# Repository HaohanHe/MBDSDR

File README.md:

# MBDSDR · AI 定义无线电（AI-defined SDR） v0.2.0

> **30 秒读懂**：这是一套把示波器/矢网/软件无线电（SDR）的每个动作封装成
> LLM 可调用工具的系统——外部 AI agent 通过 MCP 协议直接遥控真实硬件：
> 测天线、收信号、解调、解码、抓星历。**没有 mock、没有假数据**：没插硬件
> 就报空，未校准就标口径。本页「快速开始」的离线命令在隔离环境实测过，
> 实测口径与自动化契约见 [§4 离线复验](#4-离线复验本页命令的实测口径) 与 [`scripts/verify_readme.py`](scripts/verify_readme.py)。
>
> **真机实证（2026-10）**：NanoVNA-H 实测自制天线谐振与馈线时延、
> RTL-SDR 实抄 435MHz 业余频段载波、外部 agent 经 MCP 遥控收发全链路、
> 设备屏幕截图回传——全部见 [`docs/learn/agent-onboarding-runbook.md`](docs/learn/agent-onboarding-runbook.md)。

把 SDR 的接收 / 解调 / 解码 / 卫星过境 / AR 指向，全部封装成 LLM 可调用的工具（function calling），
由智能体编排成"一键工作流"。本仓库是同一套体系在**桌面（两套实现）、手机端、Python 智能体内核，
外加论文实验管线与真机工具**上的落地；不写死组件数量，实时清单以本节表格为准。

| 组件 | 位置 | 是什么 |
|---|---|---|
| Python/PySide6 桌面客户端 | [`desktop/`](desktop/README.md) | 持续维护中的完整桌面端：频谱/瀑布、星象仪全天球、AI 对话栏、真机接收链。`python desktop/main.py` 直接启动、无需编译；无硬件时默认显示诚实「未连接」空状态 |
| 原生 C++/Qt 桌面端 | [`cpp/`](cpp/README.md) | C++/Qt 原生 SDR 接收软件（UI 与 DSP 同进程，不依赖 Python 运行时）。AI 助手工具面（read/write 双态、写动作在手动模式被门拦截；**数量随版本漂移，实时口径以 `cpp/src/ai/tool_schema.cpp` 注册表为准**），并内置 ControlHub HTTP 控制通道 |
| 手机端 | [`mobile/`](mobile/README.md) | Flutter 一套代码（Android/iOS），手机作 AI 的"眼睛和手臂"：定位+罗盘指向+rtl_tcp 直连外置 SDR；经 ControlHub HTTP 只读对接桌面引擎 |
| Python 智能体内核 | [`mbdsdr_ai/`](mbdsdr_ai/README.md) | **研究原型**：注册大量 LLM 可调用工具（数量随版本漂移，实时口径见该 README §1 与运行时 `tool_registry.list_tools()`）+ 工作流引擎。这是原型期工具面，**不是**随桌面交付的工具集 |
| 论文实验管线 | [`experiments/`](experiments/README.md) | 可复现实验（Eb/N0 解码成功率 / 多普勒定轨 / AMR 基线 / LLM 基线），固定种子、逐图标口径 |
| 真机工具 | [`tools/`](tools/) | 一键只读自检 `hw_selfcheck` + 联调向导 `onboarding` |
| 重复实现台账 | [`docs/learn/dedup-ledger.md`](docs/learn/dedup-ledger.md) | 同主题多份实现的状态台账（已收敛/有意分层/待收敛）+ 成对工具自洽审计方法与已修缺陷 | 
| 能力地图 | [`docs/learn/capability-map.md`](docs/learn/capability-map.md) | 任务→积木编排对照表（气象对星接收/多普勒定轨/ASTU-1遥测/前端搭建/链路自测）+ 新积木参数速查 + 诚实边界 |
| 学习与阶段规格 | [`docs/learn/`](docs/learn/) | 上游真实源码精读（sdrpp/gnuradio/librtlsdr…）+ phase3–6 实现规格与审计 |

许可证：**MIT**（见 [`LICENSE`](LICENSE)、第三方归属 [`NOTICE.md`](NOTICE.md)）。

**工程口径**：全仓 **MIT 发布**，第三方上游项目与许可归属见 [`NOTICE.md`](NOTICE.md)；
协议栈（FT8/LRPT/CCSDS 等）按公开标准与协议事实独立实现 · LLM 工具三通道（Agent / ControlHub /
HTTP）行为一致且有测试钉住，写动作一律过人工门 · 已对 SDR++、SatDump、
nanovna-saver、NanoVNA-App、kimi-code、kilocode 六个上游项目做过源码级
克隆审计（见 [`docs/learn/`](docs/learn/)）。

---

<details open>
<summary><b>日本語 / For Japanese readers</b></summary>

**MBDSDR は「AI が計測器を直接操作するシステム」です。** SDR（ソフトウェア無線）と
ベクトル・ネットワーク・アナライザ（NanoVNA）の操作を LLM から呼び出せる
ツールとして実装し、MCP（Model Context Protocol）経由で外部エージェントが
実機を操作できます。専用機器の操作習熟コストを AI に引き渡すことが出発点です。

**実機検証済み（2026 年 10 月、ダミーデータなし）**：
NanoVNA-H による自作アンテナの共振周波数・給線路遅延の実測 / RTL-SDR による
435 MHz 帯アマチュア周波数の実キャリア受信・FM 復調 / 外部エージェントからの
MCP 遠隔操作（list_devices → connect → set_frequency → get_status）。

**ライセンスと門**：リポジトリ全体が MIT（独立実装、GPL コードの流用なし）·
LLM ツールは Agent / ControlHub / HTTP の 3 チャネルで動作が一致し、書き込みには
手動承認ゲートが必須 · SDR++・SatDump・NanoVNA-App 等の主要 OSS をクローンして
ソース監査済み。

ハードウェアなしで試す：
`python3 -m mbdsdr_ai.aigui_demo --out demo.html`（AI 編排 UI の一巡）、
`python3 -m pytest tools/hw_selfcheck/test_selfcheck.py tools/onboarding/test_onboarding.py -q`
（オフライン決定性テスト）。どちらも実機を必要としません。

</details>

---

## 快速开始

### 1. 桌面端（两套实现，按工具链选）

**Python / PySide6 桌面客户端**——无需 C++ 工具链，当前持续维护的 UI 主界面：

```bash
pip install -r requirements.txt
python desktop/main.py                                     # 无硬件时显示诚实「未连接」空状态
python desktop/main.py --theme dark                        # 可选：default / dark / high_contrast
python desktop/main.py --import-probe desktop.main_window  # 只做导入自检，不建窗口
```

依赖、打包与其它启动方式见 [`desktop/README.md`](desktop/README.md)。
不插硬件时**不默认造合成 IQ**；`--import-probe` 是在无显示环境里验证安装的最快一条命令。

**原生 C++/Qt 桌面端**——需 Qt 6.8 / librtlsdr 2.x / CMake 3.16+ 与 C++ 编译工具链：

```bash
cd cpp
cmake -S . -B build && cmake --build build -j"$(nproc)"
./build/mbdsdr        # 无硬件且未加载离线捕获文件时，显示诚实"未连接"空状态
                      # 需要合成调试信号时必须显式 --test-source / MBDSDR_TEST_SOURCE=1
                      # 设计红线：never invent synthetic IQ by default, no fake hardware is ever shown
```

依赖、测试与完整功能清单见 [`cpp/README.md`](cpp/README.md)。
两套桌面端并存、各有独立测试；没有 C++ 工具链的机器直接走上面的 Python 端，不必先编 `cpp/`。

**原生 C++/Qt 桌面端**启动后在**回环 `127.0.0.1:50732`** 起一条 ControlHub HTTP 控制通道
（具名常量 `cpp/src/core/tokens.h` 的 `kControlHttpDefaultPort`，QSettings/env 可配）：
本机浏览器开 `http://127.0.0.1:50732/` 即可查看状态 / 下命令；端点只绑回环，跨机控制走 SSH 隧道（如 `ssh -N -L 50732:127.0.0.1:50732 user@接收机`）。
Chromebook / Crostini 当远程控制端的完整拓扑与隧道步骤见 [`docs/CHROMEOS_CROSTINI_SDR.md`](docs/CHROMEOS_CROSTINI_SDR.md)。
Python/PySide6 桌面端不走这条 ControlHub 通道，别按上面的地址去找它。

### 2. 真机自检 + 联调（一条命令）

真机（RTL-SDR + GNSS + 天线）在**用户本地**；云开发环境无任何硬件透传：

```bash
# 只读自检：USB/udev、rtl_test tuner、rtl_sdr 实读丢包、声卡、GNSS 串口、Python 依赖
python3 tools/hw_selfcheck/selfcheck.py

# 一条命令从"插好 RTL-SDR"走到"出图/出报文"（ADS-B 飞机报文，1090 MHz）
python3 tools/onboarding/onboard.py --step all --freq 1090e6 --mode adsb
```

- 两条命令都可加 `--json` 输出结构化结果；**无硬件时每步明确失败原因，绝不 mock、绝不造假数据**。
- 真机用户跑完后，按 [`docs/learn/phase6/P2-hw-report-format.md`](docs/learn/phase6/P2-hw-report-format.md)
  的回传格式把 JSON 贴回。
- 用法与 FAQ 见 [`tools/onboarding/README.md`](tools/onboarding/README.md)、
  [`tools/hw_selfcheck/README.md`](tools/hw_selfcheck/README.md)。

### 3. Python 内核与论文实验

```bash
# 工具自测（离线、确定性、不碰真机）
python3 -m pytest tools/hw_selfcheck/test_selfcheck.py tools/onboarding/test_onboarding.py -q

# 复现一个仿真实验（固定种子，产物落被 gitignore 的 paper/experiments/）
python3 experiments/exp_ebno_decode.py --trials 50 --seed 20261001
```

见 [`mbdsdr_ai/README.md`](mbdsdr_ai/README.md)（工具面 / 摘除项 / 诚实标注项）与
[`experiments/README.md`](experiments/README.md)（口径红线与全部复现命令）。

### 4. 离线复验（本页命令的实测口径）

下列命令在**隔离 HOME/APPDATA、无硬件透传**的环境里真跑过（`MBDSDR_OFFLINE=1`、
`MBDSDR_NO_HW=1`、`QT_QPA_PLATFORM=offscreen`）。结果按命令性质分两类，不写会过期的通过数：

| 命令 | 无硬件时的真实行为 |
|---|---|
| `python3 tools/hw_selfcheck/selfcheck.py --json` | 退出码 1；JSON `summary` 给出 PASS/WARN/FAIL/SKIP 计数与结论「未检测到 RTL-SDR 真机设备」，逐项附 evidence 与 fix，不补假设备 |
| `python3 tools/onboarding/onboard.py --json --step detect` | 退出码 1；`detect` 步报「未检测到 RTL-SDR 设备（0bda:2838/2832）」并列修复建议，不进入采集 |
| `python3 -m pytest tools/hw_selfcheck/test_selfcheck.py tools/onboarding/test_onboarding.py -q` | 退出码 0；离线确定性用例通过，无硬件专项诚实 SKIP |
| `python3 experiments/exp_ebno_decode.py --trials 50 --seed 20261001` | 退出码 0；输出 Eb/N0 扫描与成功率，写 `paper/experiments/` 下 CSV、PNG、manifest，口径标 `synthetic`（仿真，非实测信号） |
| `python3 -m mbdsdr_ai.aigui_demo --out demo.html` | 退出码 0；生成静态 HTML 编排演示页，不碰硬件 |
| `python3 desktop/main.py --import-probe desktop.main_window` | 退出码 0；打印 `[probe] OK desktop.main_window`，不建窗口 |

**在 Windows 上**，`hw_selfcheck` 的 USB 段会走降级路径（`lsusb` 不可用 → 尝试扫 `/sys`，
而 Windows 并无该目录），
结论仍如实说明真机待办；这属于环境差异，不是脚本失败。真机接入后按 §2 重跑才有真机结论。

六条命令可一键复跑：`python3 scripts/repro_readme_offline.py`
（隔离 HOME/APPDATA、不碰真机；真机自检按预期返回 1 并如实打印，不粉饰成通过）。
复跑脚本为缩短耗时把仿真实验的 `--trials` 从上表的 50 降到 10，其余命令逐字一致；
固定种子不变，曲线形态可对照，别把两次样本量不同的数字直接比。

本页的链接、路径、命令参数与版本号由 [`scripts/verify_readme.py`](scripts/verify_readme.py)
自动校验（`python3 scripts/verify_readme.py --json`），测试钉在 `tests/test_readme_contract.py`。
文档改了、代码没跟上，守卫会直接红。

---

## 真机与云测状态（诚实声明）

- **云测环境无硬件**：无 USB / 串口 / 声卡 / GNSS。所有依赖真机的工具在云内返回诚实空态或失败
  （"请先 sdr_connect / sdr_open_iq_file / 配置地面站坐标"），不静默 mock、不补假点。
- C++ / Flutter / Python 三端的**真实硬件联调均需在用户本地真机完成后回传结果**；
  真机步骤与回传格式见 [`docs/learn/phase6/P2-hw-report-format.md`](docs/learn/phase6/P2-hw-report-format.md)。
- 云内可验证的部分（构建 offscreen + 测试信号、离线确定性测试、仿真口径实验）已在各端自测通过；
  真机专项（真实拔插、出声、USB-GNSS）标注为"待真机"，未宣称已验证。
- 三端测试基线与回归锚点见 [`AGENTS.md`](AGENTS.md) §5，随每轮工程实测更新；验证能力以**可复现命令**
  （见上方命令区）与云端 CI（`.github/workflows/ci.yml`）为准，不设数字标语——数字随时间浮动，
  写入即过期（AGENTS.md §1）。无硬件环境下的用例以诚实 SKIP 结算，换机 / 真机后需重测，不代表真机已验。
- 未解决项总账（逐项带阶段溯源）见 [`docs/learn/phase41/open-items.md`](docs/learn/phase41/open-items.md)。
- 「快速开始」里**不依赖真机**的六条命令已在隔离环境实跑，逐条真实行为见 §4；
  两条真机自检返回非零退出码是设计行为（诚实失败），不是脚本坏了。

## LLM 基线（诚实说明）

实验管线里的 LLM 基线（`experiments/exp_llm_baseline.py`）**仅在配置 API key 时才真调在线模型**。
云内 / 无 key 环境下：经典规则与 KNN 在本地真算，**LLM 整列输出 `PENDING_ONLINE_RUN`**——
不伪造数值、不联网、不花钱。key 只从环境变量读（`MBDSDR_LLM_API_KEY`），代码与文档中无任何 key 字面量。

桌面 / 移动端的 AI 聊天（`cpp/src/ai/llm_worker`）同理：无 key 或 `401/403` 时**诚实报 PENDING、不 mock 输出**；
transport 层已透传真实 HTTP 状态码（`cpp/src/ai/llm_client.cpp` 读 `HttpStatusCodeAttribute`），按码分类
（`429/5xx` 退避重试、`4xx` 终态如实报错）。但**真实在线重试 e2e 从未在带 key / 联网环境跑过**——
分类与退避路径由离线纯函数测试钉住，在线一次实跑仍属未决（见总账）。

## 受保护编码器（不内置）

DMR / P25 / C4FM 等涉及专利或许可受限的语音编码器**不内置**本仓库。需要时由用户自行上传合法的外部
解码器/二进制；系统在检测到外部组件时接线、没有时诚实标注不可用。本仓库为 **MIT 独立实现**实现，
上游项目（sdrpp / gnuradio / librtlsdr 等）的协议事实与交互范式是实现依据，
项目与许可归属见 [`NOTICE.md`](NOTICE.md)。

---

## 目录导览

```
cpp/        原生 C++/Qt 桌面 SDR（引擎/解调/录制/解码/卫星过境/世界地图/AI 助手）
mobile/     Flutter 手机端（Android/iOS）：rtl_tcp 客户端 + 解调 + 录音/回放 building blocks + GNSS
desktop/    Python/PySide6 桌面客户端（频谱/星象仪/AI 对话栏/真机链路，持续维护；启动见 desktop/README.md）
mbdsdr_ai/  Python 智能体内核：agent.py 装配、sdr_tools.py 工具面、workflow_engine、scheduler、pose
experiments/论文实验管线（common/ 公共库 + exp_*.py 脚本 + tests/）
tools/      hw_selfcheck（真机只读自检）、onboarding（联调向导）
docs/learn/ 上游精读笔记 + phase3–41 实现规格与审计（交付状态横幅见各 _PHASE*_SPEC.md 顶部；总账见 phase41/open-items.md）
paper/      论文与实验产物（被 .gitignore，生成物由脚本一键再生成）
repos/      克隆的上游源码（仅供学习，不入产品路径）
```

根目录另存历史设计稿（白皮书、IEEE 论文初稿、卫星指向雷达图）与硬件工程
（KiCad、BOM、接线表），均为阶段性交付物，不参与三端构建。

## 30 秒上手：NanoVNA 真机 dump
1. 接线：被测件接 PORT 1（S11），USB 接电脑（VID:PID 0x0483:0x5740，Windows 用 COMx）。
2. 跑：
   ```
   python3 -m mbdsdr_ai.nanovna_dump --port /dev/ttyACM0 --json-pretty --out sweep.json
   ```
3. 回传 sweep.json（+ 连接日志 version/info/cal）即可比对。
无设备可先 `--selftest` 跑通流程（合成演示，非真实测量）。详见 docs/learn/nanovna/hardware-quickstart.md。

## 工具能力（不在 README 复制浮动清单）

工具名、读写标记与域分组随版本变化，抄进首页当天就开始过期；本仓库**不在这里复刻表**。
唯一事实源与查看方式：

| 想看什么 | 去哪看 |
|---|---|
| 运行时实时清单 | Python `ToolRegistry.list_tools()` / C++ `registeredToolSpecs()`（写动作一律过手动 gate） |
| 自动生成的文档快照 | [`docs/learn/phase31/agent-tool-documentation.md`](docs/learn/phase31/agent-tool-documentation.md)（固定字段：name / description / JSON Schema / 读写标记 / 错误示例） |
| Python 内核工具面与诚实标注项 | [`mbdsdr_ai/README.md`](mbdsdr_ai/README.md) §2 |
| 任务→积木编排对照 | [`docs/learn/capability-map.md`](docs/learn/capability-map.md) |
| 域分组口径 | `docs/learn/phase31/agent-tool-documentation.md` 与 `docs/learn/phase31/_WAVE2_AGENT_LANDING.md` |

三通道（Agent / ControlHub / HTTP）行为一致且有测试钉住，写动作一律过人工门；
「没设备就报空、没校准就标口径」对所有通道同样成立。

## MCP 服务器（C++ mbdsdr-mcp 与 Python mbdsdr_ai/core/mcp_server.py）合并视图

两套 MCP server 同仓并存、互为镜像：

- **域分组一致**：两 server 的 `tools/list` 均按域分组（C++ 10 域、Python 11 域——Python 前 10 域与 C++ 同集合，另含「解码器长尾」扩展域；钉扎测试保证不漂移）。
- **C++ `mbdsdr-mcp`**：面向外部第三方 agent 的 stdio 接入面（接入细节见 `docs/learn/phase63/third-party-agent-mcp.md`），工具本体与桌面 Agent 同一套 `registeredToolSpecs()`，不另立实现。
- **Python `mbdsdr_ai/core/mcp_server.py`**：面向脚本/嵌入式控制器的本地调用面，便于在测试台与自动化脚本里直接驱动同一工具语义。
- **写工具一致门控**：两 server 的写工具统一走 `arm_manual` / 手动 gate，人在环确认，不会因接入面不同而绕过。

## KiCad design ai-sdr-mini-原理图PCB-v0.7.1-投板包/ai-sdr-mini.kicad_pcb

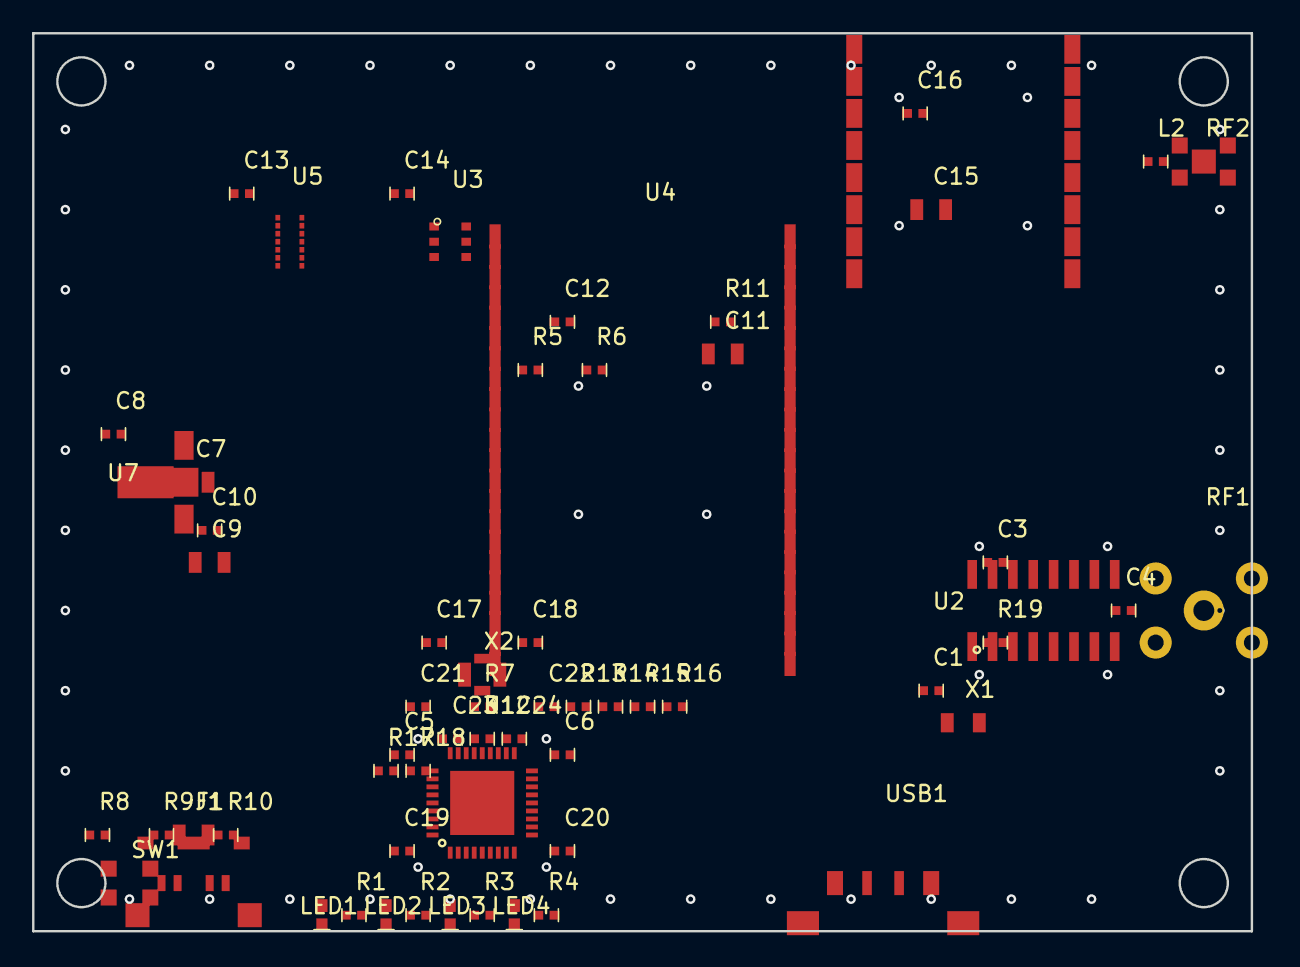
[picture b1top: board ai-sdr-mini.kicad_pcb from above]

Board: 2 copper layers, 76.0 x 56.0 mm, 62 parts (0 on the bottom side), 37 nets, no tracks yet.

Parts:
C1: 12pF; 0402
C3, C4, C5, C6, C8, C10, C12, C13, C14, C16, C19, C20, C21, C22, C23, C24: 100nF; 0402
C7, C9, C11, C15: 10uF; 0805
C17, C18: 18pF; 0402
F1: 500mA; 0805
J1: TYPE-C-6P
L2: 100nH; 0402
LED1, LED2, LED3, LED4: LED_YELLOW; 0603_LED
R1, R2, R3, R4: 1k; 0402
R5, R6, R19: 4.7k; 0402
R7, R8, R11, R13, R14, R15, R16: 10k; 0402
R9, R10: 5.1k; 0402
R12: 12k; 0402
R17, R18: 100k; 0402
RF1: SMA-F; SMA-FEMALE
RF2: UFL-F; UFL-FEMALE
SW1: TS-1101; BUTTON-3x4
U1: USB2514B-AEZC; QFN-36-6x6
U2: SI4732-A10-GSR; SOIC-16
U3: TMAG5273A1QDBVT; SOT-23-6
U4: ESP32-S3-WROOM-1-N8R8; ESP32-S3-WROOM-1
U5: BMI260; LGA-14-2.5x3
U6: ATGM336H-5NR32-G; ATGM336H-5N
U7: AMS1117-3.3; SOT-223
USB1: USB-A-F; USB-A-FEMALE
X1: 32.768kHz; CRYSTAL-3215
X2: 24MHz; CRYSTAL-3225

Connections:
5V_USB: F1.1, F1.2, J1.VBUS, R17.1, U7.3, USB1.VBUS
+3V3: C3.1, C5.1, C6.1, C7.1, C8.1, C9.1, C10.1, C11.1, C12.1, C13.1, C14.1, C15.1, C16.1, C19.1, C20.1, C21.1, C22.1, L2.1, R1.1, R2.1, R3.1, R4.1, R5.1, R6.1, R7.1, R8.1, R11.1, R19.1, U1.5, U1.10, U1.15, U1.23, U1.29, U1.36, U2.14, U3.4, U4.2, U5.1, U5.8, U6.6, U6.8, U7.2, U7.4
BTN: R8.2, SW1.1, SW1.2, U4.3
CC1: J1.CC1, R9.1
CC2: J1.CC2, R10.1
FM_IN: C4.2, U2.6
GND: C1.2, C3.2, C5.2, C6.2, C7.2, C8.2, C9.2, C10.2, C11.2, C12.2, C13.2, C14.2, C15.2, C16.2, C17.2, C18.2, C19.2, C20.2, C21.2, C22.2, C23.2, C24.2, J1.GND1, J1.GND2, J1.SH1, J1.SH2, LED1.2, LED2.2, LED3.2, LED4.2, R9.2, R10.2, R11.2, R12.2, R13.1, R14.1, R15.1, R16.1, R18.2, RF1.2, RF1.3, RF1.4, RF1.5, RF2.2, RF2.3, RF2.4, RF2.5, SW1.3, SW1.4, U1.11, U1.37, U2.7, U2.10, U2.15, U3.2, U3.3, U4.1, U5.2, U5.5, U5.9, U5.14, U6.1, U6.16, U7.1, USB1.GND, USB1.SH1, USB1.SH2, X1.2, X2.3, X2.4
GPS_ANT: L2.2, RF2.1
GPS_PPS: U4.9, U6.4
HUB_CRFLT: C23.1, U1.14
HUB_PLLFILT: C24.1, R15.2, U1.34
HUB_RBIAS: R12.1, R16.2, U1.35
HUB_RESET: R7.2, U1.26, U4.21
I2C0_SCL: R5.2, R14.2, U2.11, U3.1, U4.12, U5.3
I2C0_SDA: R6.2, R13.2, U2.12, U3.6, U4.17, U5.4
I2S_BCLK: U2.2, U4.4
I2S_DIN: U2.16, U4.7
I2S_LRCLK: U2.1, U4.5
LED1: LED1.1, R1.2
LED2: LED2.1, R2.2
LED3: LED3.1, R3.2, U4.15
LED4: LED4.1, R4.2, U4.16
RF_IN: C4.1, RF1.1, U2.8
SI4732_INT: U2.3, U4.18
SI4732_RCLK: C1.1, U2.13, X1.1
SI4732_RST: R19.2, U2.9, U4.19
UART1_RX: U4.10, U6.2
UART1_TX: U4.11, U6.3
USB_DM2: U1.3, U4.13
USB_DM3: U1.6, USB1.D-
USB_DM_UP: J1.D-, U1.30
USB_DP2: U1.4, U4.14
USB_DP3: U1.7, USB1.D+
USB_DP_UP: J1.D+, U1.31
VBUS_DET: R17.2, R18.1, U1.27
XTALIN: C17.1, U1.33, X2.1
XTALOUT: C18.1, U1.32, X2.2

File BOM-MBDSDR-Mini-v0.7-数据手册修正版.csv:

位号,型号/规格,封装,数量,立创编号,用途
U1,USB2514B-AEZC-TR,VQFN-36-EP 6x6,1,C16251,USB 2.0 4口Hub
U2,SI4732-A10-GSR,SOIC-16,1,C2155558,AM/FM/LW/SW接收+I2S输出
U3,TMAG5273A1QDBVT,SOT-23-6,1,C5220660,3轴磁力计（电子罗盘）
U4,ESP32-S3-WROOM-1-N8R8,SMD模组41脚,1,C2913201,主控WiFi+BLE+USB
U5,BMI260,LGA-14 2.5x3,1,C7544197,6轴IMU（加速度+陀螺）
U6,ATGM336H-5NR32-G,SMD模组,1,C49233943,GPS+北斗+GLONASS
U7,AMS1117-3.3,SOT-223,1,C6186,5V转3.3V LDO
J1,KH-TYPE-C-6P 卧贴,SMD 6P,1,,Type-C供电+数据
USB1,USB-A母座卧贴,SMD,1,,USB扩展口
RF1,BWSMA-KE-Z001 SMA直插,直插,1,,SDR天线
RF2,HMTConn u.FL贴片,SMD,1,,GPS天线
SW1,TS-1101-C-W 按钮,SMD,1,,ESP32复位
LED1-4,LTSTC190KYKT 黄光,0603,4,,状态指示
X1,FC-135 32.768kHz 无源晶振,3215,1,,SI4732参考时钟
X2,24MHz 无源晶振,3225,1,,USB2514B时钟
C1,12pF C0G ±5% 50V,0402,1,,SI4732晶振负载
C17,C18,18pF C0G ±5% 50V,0402,2,,USB2514B晶振负载
C3,C4,C5,C6,C8,C10,C12,C13,C14,C16,C19,C20,C21,C22,C23,C24,100nF X7R ±10% 50V,0402,16,,去耦/隔直/滤波
C7,C9,C11,C15,10μF X5R ±20% 16V,0805,4,,电源滤波
R1-R4,1kΩ ±1% 1/16W,0402,4,,LED限流
R5,R6,4.7kΩ ±1%,0402,2,,I2C上拉
R7,R8,R11,R13,R14,R15,R16,10kΩ ±1%,0402,7,,上拉/下拉/配置
R9,R10,5.1kΩ ±1%,0402,2,,Type-C CC下拉
R12,12kΩ ±1%,0402,1,,USB2514B RBIAS偏置
R17,R18,100kΩ ±1%,0402,2,,VBUS_DET分压
R19,4.7kΩ ±1%,0402,1,,SI4732 RST上拉
L1,68nH（可选不焊）,0402,0,,AM天线匹配
L2,100nH,0402,1,,GPS有源天线馈电感
F1,自恢复保险丝 500mA,0805,1,,Type-C输入过流保护

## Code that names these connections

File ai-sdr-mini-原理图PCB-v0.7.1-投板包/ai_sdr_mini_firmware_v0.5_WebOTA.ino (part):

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#include <esp_task_wdt.h>

// ==================== 引脚定义 (ESP32-S3-WROOM-1-N8R8) ====================
#define PIN_I2C0_SCL     8    // IO8  -> I2C0 SCL (SI4732 + BMI260 + TMAG5273)
#define PIN_I2C0_SDA     9    // IO9  -> I2C0 SDA
#define PIN_I2S_BCLK      4    // IO4  <- SI4732 DCLK (I2S位时钟输入)
#define PIN_I2S_LRCLK     5    // IO5  <- SI4732 LOUT/DFS (I2S帧时钟输入)
#define PIN_I2S_DIN       7    // IO7  <- SI4732 ROUT/DOUT (I2S数据输入)
#define PIN_GPS_RX        17   // IO17 -> GPS TXD (UART1 RX)
#define PIN_GPS_TX        18   // IO18 -> GPS RXD (UART1 TX)
#define PIN_GPS_PPS       16   // IO16 -> GPS PPS
#define PIN_SI4732_INT    10   // IO10 -> SI4732 INTB/GPO2
#define PIN_SI4732_RST    11   // IO11 -> SI4732 RST (与IMU_INT复用, 见注)
#define PIN_HUB_RESET     21   // IO21 -> USB2514B RESET_N
#define PIN_LED1          1    // IO1  -> LED1 电源/运行 (黄)
#define PIN_LED2          2    // IO2  -> LED2 SDR接收 (黄)
#define PIN_LED3          3    // IO3  -> LED3 GPS定位 (黄)
#define PIN_LED4          46   // IO46 -> LED4 AI/录音 (黄)
#define PIN_BUTTON        0    // IO0  -> 复位按钮 (BOOT键复用)

// 注: SI4732_RST和IMU_INT在v0.7连接表中都接到IO11, 软件上SI4732复位时
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}

void si4732_reset() {
  pinMode(PIN_SI4732_RST, OUTPUT);
  digitalWrite(PIN_SI4732_RST, LOW);
  delay(10);
  digitalWrite(PIN_SI4732_RST, HIGH);
  delay(10);
}

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  };
  
  i2s_pin_config_t pin_config = {
    .bck_io_num = PIN_I2S_BCLK,
    .ws_io_num = PIN_I2S_LRCLK,
    .data_out_num = I2S_PIN_NO_CHANGE,
    .data_in_num = PIN_I2S_DIN
  };
  
  i2s_driver_install(I2S_PORT, &i2s_config, 0, NULL);
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
// ==================== LED 控制 ====================
void led_init() {
  pinMode(PIN_LED1, OUTPUT);
  pinMode(PIN_LED2, OUTPUT);
  pinMode(PIN_LED3, OUTPUT);
  pinMode(PIN_LED4, OUTPUT);
  digitalWrite(PIN_LED1, LOW);  // 共阳? 实际是阴极接GPIO, 所以HIGH=灭, LOW=亮
  digitalWrite(PIN_LED2, LOW);
  digitalWrite(PIN_LED3, LOW);
  digitalWrite(PIN_LED4, LOW);
}

void led_set(uint8_t pin, LedPattern pattern) {
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  static bool led_state[4] = {false,false,false,false};
  static int double_phase[4] = {0,0,0,0};
  uint32_t now = millis();
  uint8_t idx = pin - PIN_LED1;
  
  switch (pattern) {
    case LED_OFF:
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
void led_task(void* pvParameters) {
  while (1) {
    led_set(PIN_LED1, led1_pattern);
    led_set(PIN_LED2, led2_pattern);
    led_set(PIN_LED3, led3_pattern);
    led_set(PIN_LED4, led4_pattern);
    vTaskDelay(pdMS_TO_TICKS(10));
  }
}
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  led1_pattern = LED_ON;
  
  // 初始化I2C
  Wire.begin(PIN_I2C0_SDA, PIN_I2C0_SCL, 400000);
  Serial.println("[I2C] Init OK (400kHz)");
  
  // 复位SI4732
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  audio_mutex = xSemaphoreCreateMutex();
  
  // USB Hub复位
  pinMode(PIN_HUB_RESET, OUTPUT);
  digitalWrite(PIN_HUB_RESET, LOW);
  delay(10);
  digitalWrite(PIN_HUB_RESET, HIGH);
  Serial.println("[USB2514B] Reset done");
  
  // WiFi AP模式
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

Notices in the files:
ai-sdr-mini-原理图PCB-v0.7.1-投板包/ai_sdr_mini_firmware_v0.5_WebOTA.ino:
全开源 GPL-3.0
